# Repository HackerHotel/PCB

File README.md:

# PCB

This repository hosts the board files for the HackerHotel 2019 badge.

This is an EAGLE 8 (?) project. It should be possible to import it in
[KiCad](https://kicad-pcb.org)

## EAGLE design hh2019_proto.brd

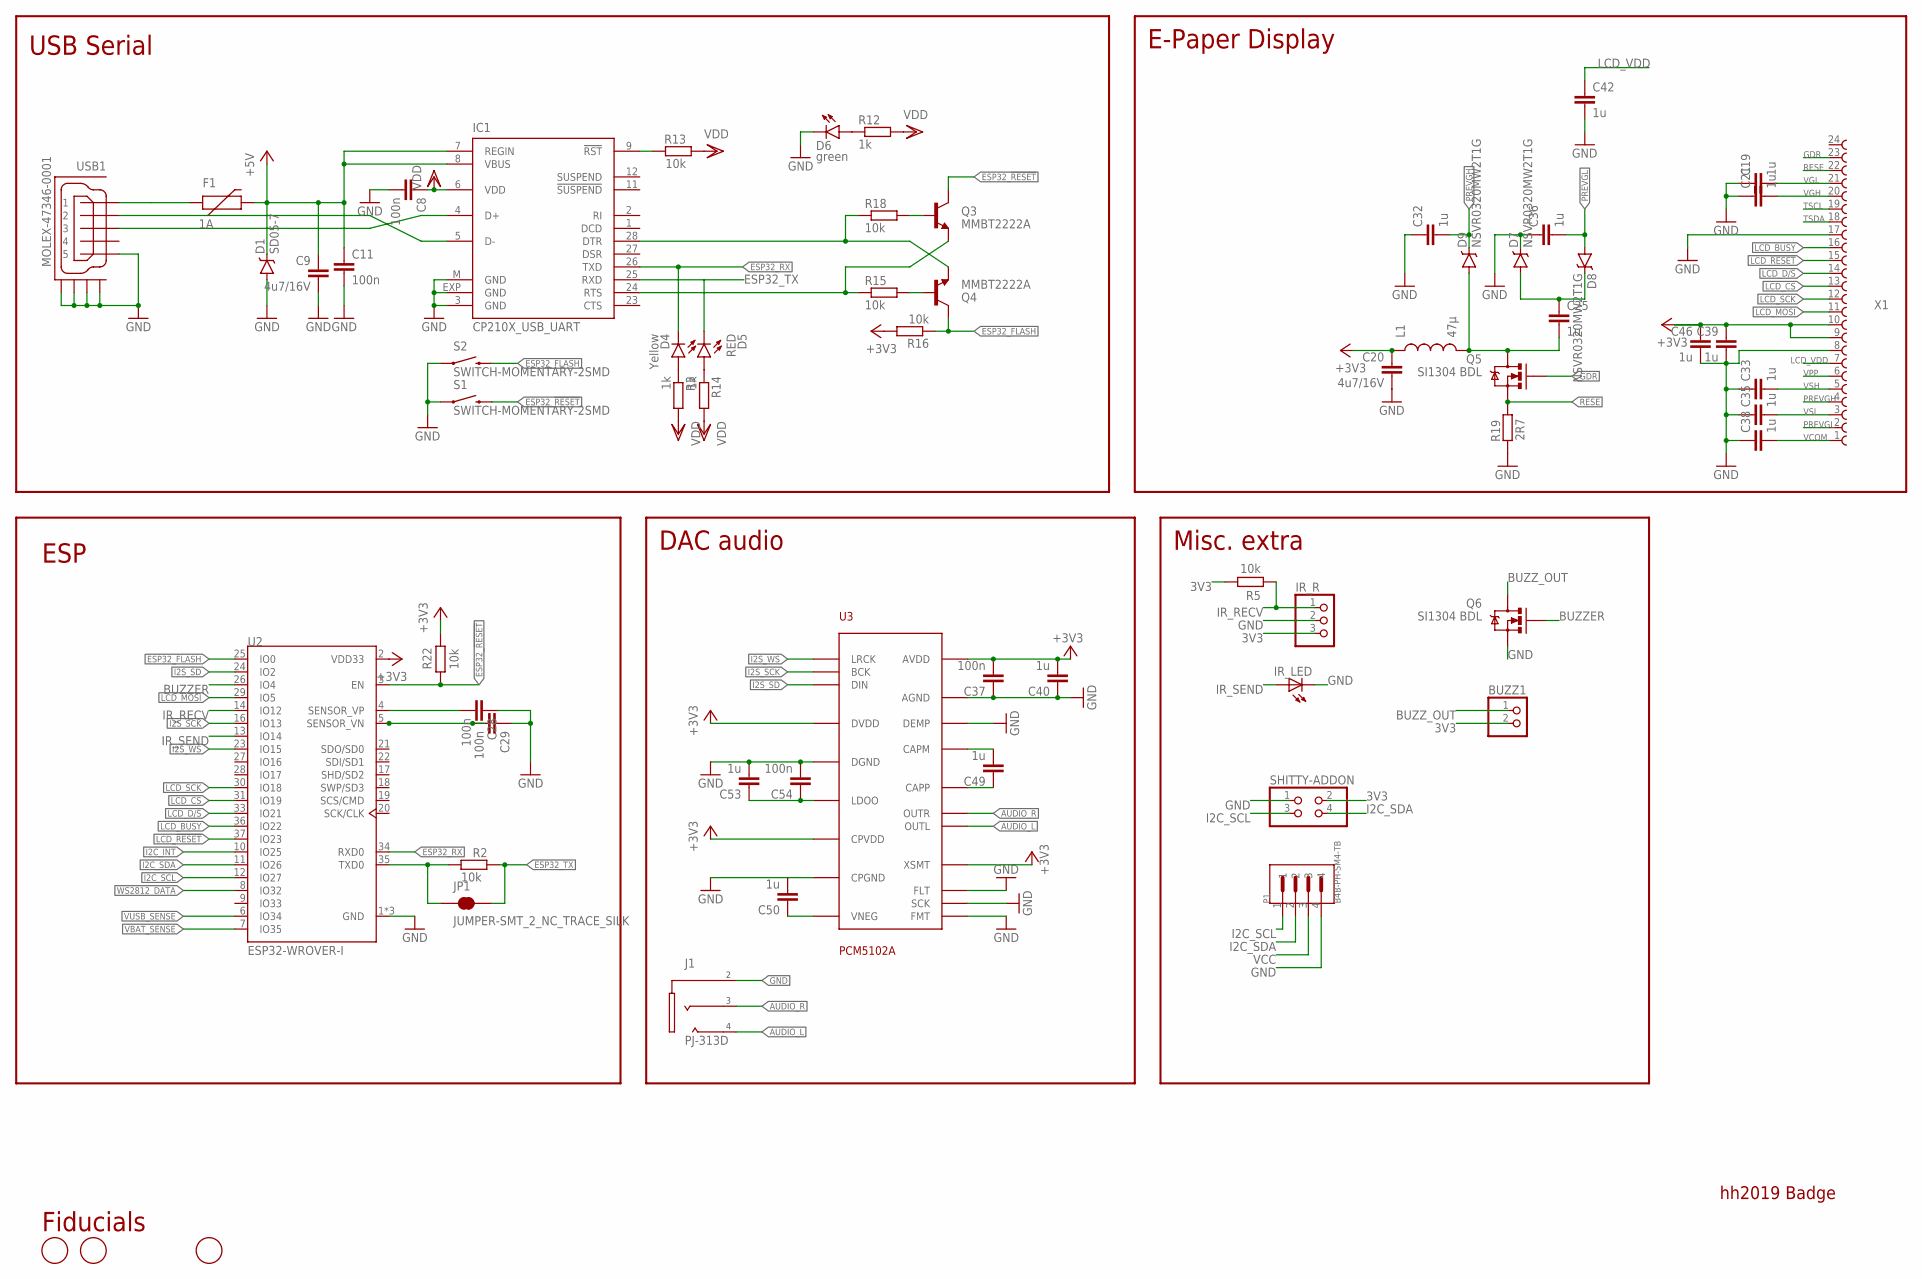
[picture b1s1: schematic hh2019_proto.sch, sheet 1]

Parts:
BUZZ1: PINHD-1X2; 1X02
C8, C11, C28, C29: 100n; C0603-DASHES; PARTNO GRM188R71H104KA93D
C9, C20: 4u7/16V; C0805; PARTNO GRM21BR61C475KA88K
C19, C21, C25, C32, C33, C35, C36, C38, C39, C42, C46: 1u; C0603-DASHES; PARTNO GRM188R61E105KA12D
C37, C54: 100n; C0603
C40, C49, C50, C53: 1u; C0603
D1: SD05-7; SOD-323; PARTNO SD05-7
D4: Yellow; LED-0603
D5: RED; LED-0603
D6: green; LED-0603
D7, D8, D9: NSVR0320MW2T1G; SOD-323; PARTNO BAT20JFILM
F1: 1A; PTC-1206
FD1, FD4, FD5: FIDUCIAL; FIDUCIAL_1MM; PARTNO NAP
IC1: CP210X_USB_UART; MLP28; PARTNO CP2102-GMR
IR_LED: LED5MM
IR_R: PINHD-1X3; 1X03
J1: PJ-313D
JP1: JUMPER-SMT_2_NC_TRACE_SILK; SMT-JUMPER_2_NC_TRACE_SILK
L1: 47µ; 1210; PARTNO NLCV32T-220K-EF
P1: B4B-PH-SM4-TB; JST_B4B-PH-SM4-TB
Q3, Q4: MMBT2222A; SOT23-3; PARTNO BC817-25,215
Q5, Q6: SI1304 BDL; SOT323; PARTNO SI1308EDL-T1-GE3
R2, R5, R13, R15, R16, R18, R22: 10k; R0603-DASHES; PARTNO ERJ-3GEYJ103V
R3, R12, R14: 1k; R0603-DASHES; PARTNO ERJ-3GEYJ102V
R19: 2R7; R0603-DASHES; PARTNO ERJ-3GEYJ5R1V
S1, S2: SWITCH-MOMENTARY-2SMD; TACTILE-SWITCH-SMD; PARTNO SKQGABE010
SHITTY-ADDON: PINHD-2X2; 2X02
U2: ESP32-WROVER-I; XCVR_ESP32-WROVER-I
U3: PCM5102A
USB1: MOLEX-47346-0001; MOLEX-47364-0001; PARTNO 10118192-0001LF
X1: 68712414022; PARTNO 68712414022

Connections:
3V3: BUZZ1.2, C20.1, C37.2, C39.1, C40.2, C46.1, IR_R.3, L1.1, R5.1, R16.2, R22.1, SHITTY-ADDON.2, U2.2 (VDD33), U3.P$1 (CPVDD), U3.P$8 (AVDD), U3.P$17 (XSMT), U3.P$20 (DVDD), X1.9, X1.10; also elsewhere on the board
+5V: C9.1, C11.1, D1.C, F1.2, IC1.7 (REGIN), IC1.8 (VBUS); also elsewhere on the board
AUDIO_L: J1.4_1 (4), J1.4_2 (4), U3.P$6 (OUTL)
AUDIO_R: J1.3_1 (3), J1.3_2 (3), U3.P$7 (OUTR)
BUZZER: Q6.1 (G), U2.26 (IO4)
BUZZ_OUT: BUZZ1.1, Q6.3 (D)
CAPM: C49.2, U3.P$4 (CAPM)
CAPP: C49.1, U3.P$2 (CAPP)
ESP32_!RESET: Q3.3 (C), R22.2, S1.3 (2), U2.3 (EN)
ESP32_FLASH: Q4.3 (C), R16.1, S2.3 (2), U2.25 (IO0)
ESP32_RX: D4.C, IC1.26 (TXD), U2.34 (RXD0)
ESP32_TX: D5.C, IC1.25 (RXD), JP1.2, R2.1
ESP32_TX_PRE: JP1.1, R2.2, U2.35 (TXD0)
GDR: Q5.1 (G), X1.23
GND: C8.2, C9.2, C11.2, C19.1, C20.2, C21.1, C28.1, C29.1, C32.1, C33.1, C35.1, C36.1, C37.1, C38.1, C39.2, C40.1, C42.2, C46.2, C50.2, C53.2, C54.2, D1.A, D6.C, D7.C, IC1.3 (GND), IC1.EXP (GND), IC1.M (GND), IR_LED.K (C), IR_R.2, J1.2_1 (2), J1.2_2 (2), P1.4, Q6.2 (S), R19.2, S1.1, S2.1, SHITTY-ADDON.1, U2.1 (GND), U2.15 (GND), U2.38 (GND), U3.P$3 (CPGND), U3.P$9 (AGND), U3.P$10 (DEMP), U3.P$11 (FLT), U3.P$12 (SCK), U3.P$16 (FMT), U3.P$19 (DGND), USB1.5, USB1.GND1, USB1.GND2, USB1.GND3, USB1.GND4, X1.8, X1.17; also elsewhere on the board
I2C_INT: U2.10 (IO25); also elsewhere on the board
I2C_SCL: P1.1, SHITTY-ADDON.3, U2.12 (IO27); also elsewhere on the board
I2C_SDA: P1.2, SHITTY-ADDON.4, U2.11 (IO26); also elsewhere on the board
I2S_SCK: U2.16 (IO13), U3.P$13 (BCK)
I2S_SD: U2.24 (IO2), U3.P$14 (DIN)
I2S_WS: U2.23 (IO15), U3.P$15 (LRCK)
IR_RECV: IR_R.1, R5.2, U2.14 (IO12)
IR_SEND: IR_LED.A, U2.13 (IO14)
LCD_!RESET: U2.37 (IO23), X1.15
LCD_BUSY: U2.36 (IO22), X1.16
LCD_CS: U2.31 (IO19), X1.13
LCD_D/!S: U2.33 (IO21), X1.14
LCD_MOSI: U2.29 (IO5), X1.11
LCD_SCK: U2.30 (IO18), X1.12
LCD_VDD: C42.1, X1.7
LDO0: C53.1, C54.1, U3.P$18 (LDOO)
unnamed: IC1.24 (RTS), Q3.2 (E), R15.1
unnamed: IC1.28 (DTR), Q4.2 (E), R18.1
unnamed: Q4.1 (B), R15.2
unnamed: Q3.1 (B), R18.2
unnamed: C25.1, D7.A, D8.C
unnamed: C25.2, D9.A, L1.2, Q5.3 (D)
unnamed: D6.A, R12.1
unnamed: D4.A, R3.1
unnamed: D5.A, R14.1
unnamed: F1.1, USB1.1
unnamed: C28.2, U2.4 (SENSOR_VP)
unnamed: C29.2, U2.5 (SENSOR_VN)
PREVGH: C32.2, D9.C, X1.4
PREVGL: C36.2, D8.A, X1.2
RESE: Q5.2 (S), R19.1, X1.22
RST: IC1.9 (!RST), R13.2
TSCL: X1.19
TSDA: X1.18
USB_DN_CON: IC1.5 (D-), USB1.2
USB_DP_CON: IC1.4 (D+), USB1.3
VBAT_SENSE: U2.7 (IO35); also elsewhere on the board
VCC: P1.3; also elsewhere on the board
VCOM: C38.2, X1.1
VDD: C8.1, IC1.6 (VDD), R3.2, R12.2, R13.1, R14.2
VGH: C21.2, X1.20
VGL: C19.2, X1.21
VNEG: C50.1, U3.P$5 (VNEG)
VPP: X1.6
VSH: C33.2, X1.5
VSL: C35.2, X1.3
VUSB_SENSE: U2.6 (IO34); also elsewhere on the board
WS2812_DATA: U2.8 (IO32); also elsewhere on the board

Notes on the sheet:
USB Serial
E-Paper Display
ESP
Fiducials
hh2019 Badge
DAC audio
Misc. extra

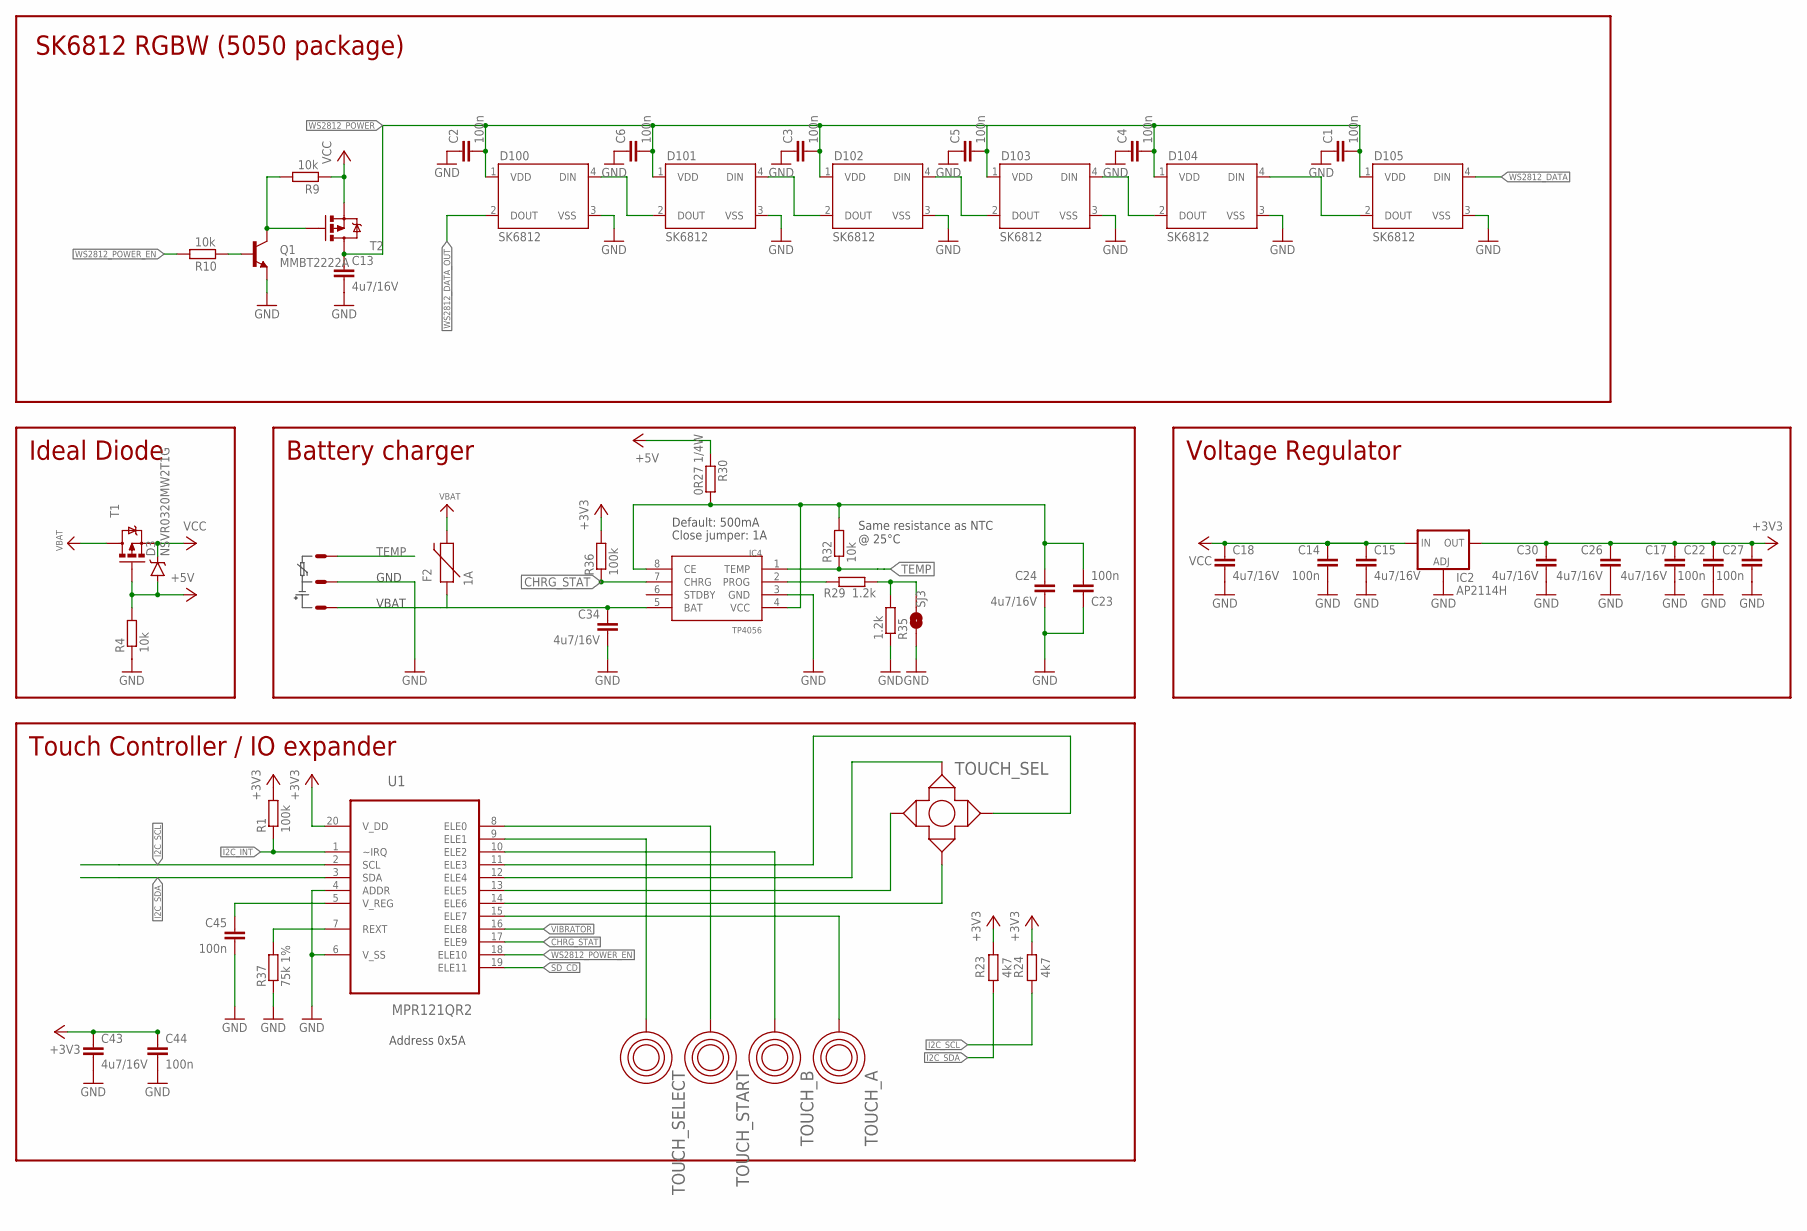
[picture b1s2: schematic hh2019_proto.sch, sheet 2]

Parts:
C1, C2, C3, C4, C5, C6, C14, C22, C23, C27, C44, C45: 100n; C0603-DASHES; PARTNO GRM188R71H104KA93D
C13, C15, C17, C18, C24, C26, C30, C34, C43: 4u7/16V; C0805; PARTNO GRM21BR61C475KA88K
D3: NSVR0320MW2T1G; SOD-323; PARTNO BAT20JFILM
D100, D101, D102, D103, D104, D105: SK6812; WS2812B; PARTNO SK6812
F2: 1A; PTC-1206
IC2: AP2114H; SOT223; PARTNO AP7215-33YG-13
IC4: TP4056; SOP-8
Q1: MMBT2222A; SOT23-3; PARTNO BC817-25,215
R1, R36: 100k; R0603-DASHES; PARTNO ERJ-3GEYJ104V
R4, R9, R10: 10k; R0603-DASHES; PARTNO ERJ-3GEYJ103V
R23, R24: 4k7; R0603-DASHES; PARTNO ERJ-3GEYJ103V
R29, R35: 1.2k; R0603-DASHES; PARTNO ERJ-3GEYJ222V
R30: 0R27 1/4W; R1206; PARTNO ERJ-3GEYJ154V
R32: 10k; R0603-DASHES; PARTNO ERJ-3GEYJ154V
R37: 75k 1%; R0603-DASHES; PARTNO ERJ-3GEYJ104V
SJ3: JUMPER-PAD-2-NOYES_SILK; PAD-JUMPER-2-NO_YES_SILK; PARTNO NAP
T1, T2: MOSFET-PCHANNEL; SOT23-3
TOUCH_A: TOUCHROUND; TOUCH_BUTTON; PARTNO NAP
TOUCH_B: TOUCHROUND; TOUCH_BUTTON; PARTNO NAP
TOUCH_SEL: TOUCH_CROSS; PARTNO NAP
TOUCH_SELECT: TOUCHSELECT; TOUCH_SELECT
TOUCH_START: TOUCHSELECT; TOUCH_SELECT
U1: MPR121QR2; QFN40P300X300X60-20N
X4: JST-PH3

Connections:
3V3: C17.1, C22.1, C26.1, C27.1, C30.1, C43.1, C44.1, IC2.4 (OUT), R1.2, R23.1, R24.1, R36.2, U1.20 (V_DD); also elsewhere on the board
+5V: D3.A, R4.2, R30.1, T1.1 (G); also elsewhere on the board
BAT: C34.1, F2.1, IC4.5 (BAT), X4.3
CE: C23.2, C24.1, IC4.4 (VCC), IC4.8 (CE), R30.2, R32.2
CHRG_STAT: IC4.7 (CHRG), R36.1, U1.17 (ELE9)
ELE0: TOUCH_START.P$1, U1.8 (ELE0)
ELE1: TOUCH_SELECT.P$1, U1.9 (ELE1)
ELE2: TOUCH_B.P$1, U1.10 (ELE2)
ELE3: TOUCH_SEL.R (RIGHT), U1.11 (ELE3)
ELE4: TOUCH_SEL.UP, U1.12 (ELE4)
ELE5: TOUCH_SEL.L (LEFT), U1.13 (ELE5)
ELE6: TOUCH_SEL.D (DOWN), U1.14 (ELE6)
ELE7: TOUCH_A.P$1, U1.15 (ELE7)
GND: C1.1, C2.1, C3.1, C4.1, C5.1, C6.1, C13.2, C14.2, C15.2, C17.2, C18.2, C22.2, C23.1, C24.2, C26.2, C27.2, C30.2, C34.2, C43.2, C44.2, C45.2, D100.3 (VSS), D101.3 (VSS), D102.3 (VSS), D103.3 (VSS), D104.3 (VSS), D105.3 (VSS), IC2.1 (ADJ), IC4.3 (GND), Q1.2 (E), R4.1, R35.2, R37.1, SJ3.1, U1.4 (ADDR), U1.6 (V_SS), X4.2; also elsewhere on the board
I2C_INT: R1.1, U1.1 (~IRQ); also elsewhere on the board
I2C_SCL: R24.2, U1.2 (SCL); also elsewhere on the board
I2C_SDA: R23.2, U1.3 (SDA); also elsewhere on the board
unnamed: D100.4 (DIN), D101.2 (DOUT)
unnamed: D103.4 (DIN), D104.2 (DOUT)
unnamed: D104.4 (DIN), D105.2 (DOUT)
unnamed: R29.2, R35.1, SJ3.2
unnamed: D101.4 (DIN), D102.2 (DOUT)
unnamed: C45.1, U1.5 (V_REG)
unnamed: R37.2, U1.7 (REXT)
unnamed: D102.4 (DIN), D103.2 (DOUT)
unnamed: Q1.1 (B), R10.2
unnamed: Q1.3 (C), R9.1, T2.1 (G)
PROG: IC4.2 (PROG), R29.1
SD_CD: U1.19 (ELE11)
TEMP: IC4.1 (TEMP), R32.1, X4.1
VBAT: F2.2, T1.3 (D); also elsewhere on the board
VCC: C14.1, C15.1, C18.1, D3.C, IC2.3 (IN), R9.2, T1.2 (S), T2.2 (S); also elsewhere on the board
VIBRATOR: U1.16 (ELE8)
WS2812_DATA: D105.4 (DIN); also elsewhere on the board
WS2812_DATA_OUT: D100.2 (DOUT)
WS2812_POWER: C1.2, C2.2, C3.2, C4.2, C5.2, C6.2, C13.1, D100.1 (VDD), D101.1 (VDD), D102.1 (VDD), D103.1 (VDD), D104.1 (VDD), D105.1 (VDD), T2.3 (D)
WS2812_POWER_EN: R10.1, U1.18 (ELE10)

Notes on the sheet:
Voltage Regulator
Battery charger
Ideal Diode
Default: 500mA
Close jumper: 1A
GND
VBAT
Same resistance as NTC @ 25°C
SK6812 RGBW (5050 package)
Touch Controller / IO expander
Address 0x5A

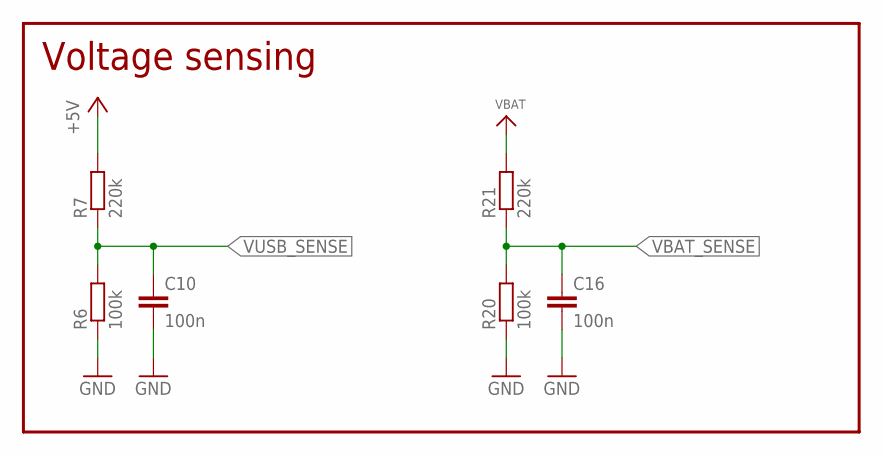
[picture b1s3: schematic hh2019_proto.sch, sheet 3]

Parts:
C10, C16: 100n; C0603-DASHES; PARTNO GRM188R71H104KA93D
R6, R20: 100k; R0603-DASHES; PARTNO ERJ-3GEYJ104V
R7, R21: 220k; R0603-DASHES; PARTNO ERJ-3GEYJ224V

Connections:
+5V: R7.2; also elsewhere on the board
GND: C10.2, C16.2, R6.1, R20.1; also elsewhere on the board
VBAT: R21.2; also elsewhere on the board
VBAT_SENSE: C16.1, R20.2, R21.1; also elsewhere on the board
VUSB_SENSE: C10.1, R6.2, R7.1; also elsewhere on the board

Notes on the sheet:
Voltage sensing

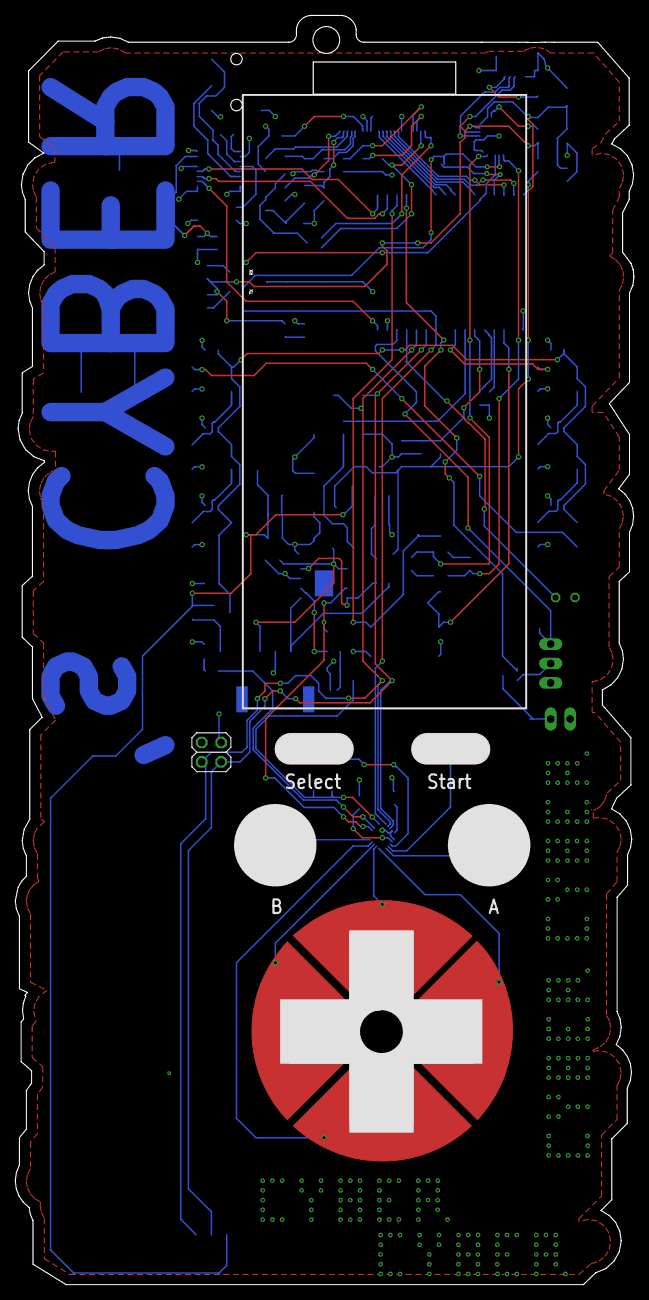
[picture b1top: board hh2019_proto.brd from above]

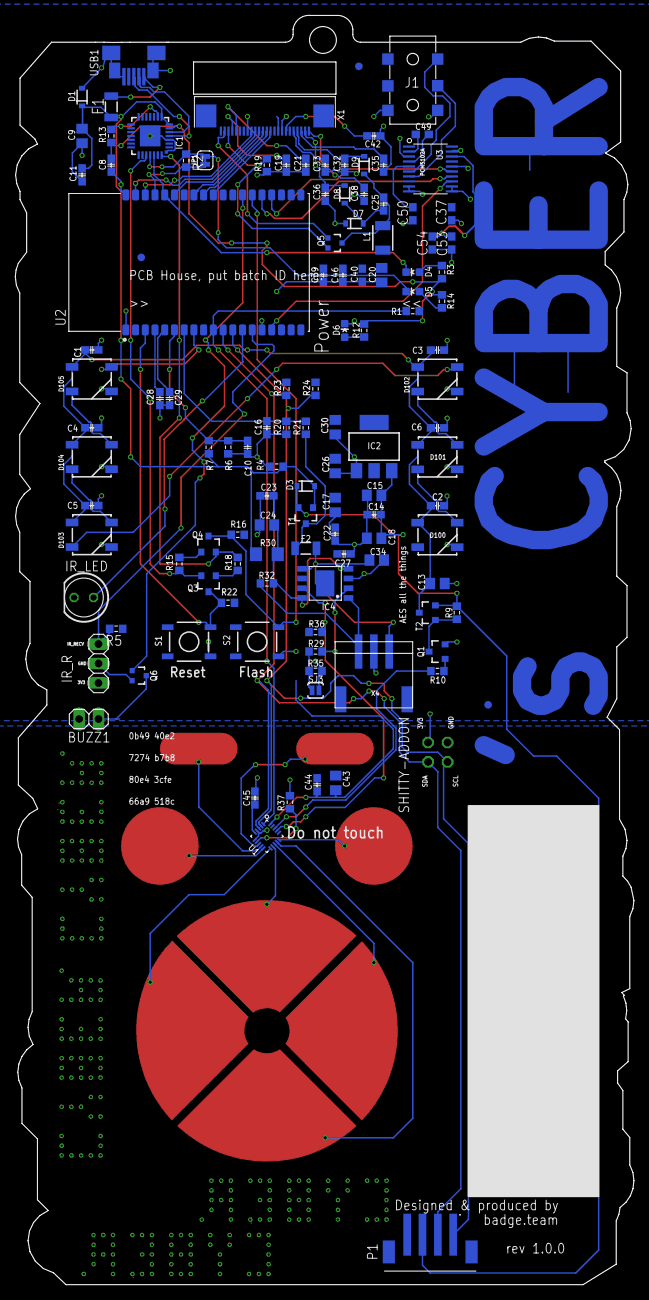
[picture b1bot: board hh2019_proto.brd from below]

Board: 2 copper layers, 80.8 x 165.7 mm, 124 parts (118 on the bottom side), 86 nets.

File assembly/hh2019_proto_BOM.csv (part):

"Part";"Value";"Device";"Package";"Description";"AVAILABILITY";"DESCRIPTION";"DIGI-KEY_PART_NUMBER";"DIGI-KEY_PURCHASE_URL";"MF";"MP";"MPN";"OC_FARNELL";"OC_NEWARK";"PACKAGE";"PARTNO";"PRICE";"PROD_ID";"SPICEPREFIX";"SUPPLIER";"VALUE";
"BUZZ1";"";"PINHD-1X2";"1X02";"PIN HEADER";"";"";"";"";"";"";"";"";"";"";"";"";"";"";"";"";
"C1";"100n";"C0603-DASHES";"C0603-DASHES";"";"";"";"";"";"";"";"";"";"";"";"GRM188R71H104KA93D";"";"";"";"";"";
"C2";"100n";"C0603-DASHES";"C0603-DASHES";"";"";"";"";"";"";"";"";"";"";"";"GRM188R71H104KA93D";"";"";"";"";"";
"C3";"100n";"C0603-DASHES";"C0603-DASHES";"";"";"";"";"";"";"";"";"";"";"";"GRM188R71H104KA93D";"";"";"";"";"";
"C4";"100n";"C0603-DASHES";"C0603-DASHES";"";"";"";"";"";"";"";"";"";"";"";"GRM188R71H104KA93D";"";"";"";"";"";
"C5";"100n";"C0603-DASHES";"C0603-DASHES";"";"";"";"";"";"";"";"";"";"";"";"GRM188R71H104KA93D";"";"";"";"";"";
"C6";"100n";"C0603-DASHES";"C0603-DASHES";"";"";"";"";"";"";"";"";"";"";"";"GRM188R71H104KA93D";"";"";"";"";"";
"C8";"100n";"C0603-DASHES";"C0603-DASHES";"";"";"";"";"";"";"";"";"";"";"";"GRM188R71H104KA93D";"";"";"";"";"";
"C9";"4u7/16V";"C-EUC0805";"C0805";"CAPACITOR, European symbol";"";"";"";"";"";"";"";"";"";"";"GRM21BR61C475KA88K";"";"";"";"";"";
"C10";"100n";"C0603-DASHES";"C0603-DASHES";"";"";"";"";"";"";"";"";"unknown";"";"";"GRM188R71H104KA93D";"";"";"";"";"";
"C11";"100n";"C0603-DASHES";"C0603-DASHES";"";"";"";"";"";"";"";"";"";"";"";"GRM188R71H104KA93D";"";"";"";"";"";
"C13";"4u7/16V";"C-EUC0805";"C0805";"CAPACITOR, European symbol";"";"";"";"";"";"";"";"";"";"";"GRM21BR61C475KA88K";"";"";"";"";"";
"C14";"100n";"C0603-DASHES";"C0603-DASHES";"";"";"";"";"";"";"";"";"";"";"";"GRM188R71H104KA93D";"";"";"";"";"";
"C15";"4u7/16V";"C-EUC0805";"C0805";"CAPACITOR, European symbol";"";"";"";"";"";"";"";"";"";"";"GRM21BR61C475KA88K";"";"";"";"";"";
"C16";"100n";"C0603-DASHES";"C0603-DASHES";"";"";"";"";"";"";"";"";"unknown";"";"";"GRM188R71H104KA93D";"";"";"";"";"";
"C17";"4u7/16V";"C-EUC0805";"C0805";"CAPACITOR, European symbol";"";"";"";"";"";"";"";"";"";"";"GRM21BR61C475KA88K";"";"";"";"";"";
"C18";"4u7/16V";"C-EUC0805";"C0805";"CAPACITOR, European symbol";"";"";"";"";"";"";"";"";"";"";"GRM21BR61C475KA88K";"";"";"";"";"";
"C19";"1u";"C0603-DASHES";"C0603-DASHES";"";"";"";"";"";"";"";"";"";"";"";"GRM188R61E105KA12D";"";"";"";"";"";
"C20";"4u7/16V";"C-EUC0805";"C0805";"CAPACITOR, European symbol";"";"";"";"";"";"";"";"";"";"";"GRM21BR61C475KA88K";"";"";"";"";"";
"C21";"1u";"C0603-DASHES";"C0603-DASHES";"";"";"";"";"";"";"";"";"";"";"";"GRM188R61E105KA12D";"";"";"";"";"";
"C22";"100n";"C0603-DASHES";"C0603-DASHES";"";"";"";"";"";"";"";"";"";"";"";"GRM188R71H104KA93D";"";"";"";"";"";
"C23";"100n";"C0603-DASHES";"C0603-DASHES";"";"";"";"";"";"";"";"";"";"";"";"GRM188R71H104KA93D";"";"";"";"";"";
"C24";"4u7/16V";"C-EUC0805";"C0805";"CAPACITOR, European symbol";"";"";"";"";"";"";"";"";"";"";"GRM21BR61C475KA88K";"";"";"";"";"";
"C25";"1u";"C0603-DASHES";"C0603-DASHES";"";"";"";"";"";"";"";"";"";"";"";"GRM188R61E105KA12D";"";"";"";"";"";
"C26";"4u7/16V";"C-EUC0805";"C0805";"CAPACITOR, European symbol";"";"";"";"";"";"";"";"";"";"";"GRM21BR61C475KA88K";"";"";"";"";"";
"C27";"100n";"C0603-DASHES";"C0603-DASHES";"";"";"";"";"";"";"";"";"";"";"";"GRM188R71H104KA93D";"";"";"";"";"";
"C28";"100n";"C0603-DASHES";"C0603-DASHES";"";"";"";"";"";"";"";"";"unknown";"";"";"GRM188R71H104KA93D";"";"";"";"";"";
"C29";"100n";"C0603-DASHES";"C0603-DASHES";"";"";"";"";"";"";"";"";"unknown";"";"";"GRM188R71H104KA93D";"";"";"";"";"";
"C30";"4u7/16V";"C-EUC0805";"C0805";"CAPACITOR, European symbol";"";"";"";"";"";"";"";"";"";"";"GRM21BR61C475KA88K";"";"";"";"";"";
"C32";"1u";"C0603-DASHES";"C0603-DASHES";"";"";"";"";"";"";"";"";"";"";"";"GRM188R61E105KA12D";"";"";"";"";"";
"C33";"1u";"C0603-DASHES";"C0603-DASHES";"";"";"";"";"";"";"";"";"";"";"";"GRM188R61E105KA12D";"";"";"";"";"";
"C34";"4u7/16V";"C-EUC0805";"C0805";"CAPACITOR, European symbol";"";"";"";"";"";"";"";"";"";"";"GRM21BR61C475KA88K";"";"";"";"";"";
"C35";"1u";"C0603-DASHES";"C0603-DASHES";"";"";"";"";"";"";"";"";"";"";"";"GRM188R61E105KA12D";"";"";"";"";"";
"C36";"1u";"C0603-DASHES";"C0603-DASHES";"";"";"";"";"";"";"";"";"";"";"";"GRM188R61E105KA12D";"";"";"";"";"";
"C37";"100n";"C-EUC0603";"C0603";"CAPACITOR, European symbol";"";"";"";"";"";"";"";"";"";"";"";"";"";"C";"";"";
"C38";"1u";"C0603-DASHES";"C0603-DASHES";"";"";"";"";"";"";"";"";"";"";"";"GRM188R61E105KA12D";"";"";"";"";"";
"C39";"1u";"C0603-DASHES";"C0603-DASHES";"";"";"";"";"";"";"";"";"";"";"";"GRM188R61E105KA12D";"";"";"";"";"";
"C40";"1u";"C-EUC0603";"C0603";"CAPACITOR, European symbol";"";"";"";"";"";"";"";"";"";"";"";"";"";"C";"";"";
"C42";"1u";"C0603-DASHES";"C0603-DASHES";"";"";"";"";"";"";"";"";"";"";"";"GRM188R61E105KA12D";"";"";"";"";"";
"C43";"4u7/16V";"C-EUC0805";"C0805";"CAPACITOR, European symbol";"";"";"";"";"";"";"";"";"";"";"GRM21BR61C475KA88K";"";"";"";"";"";
"C44";"100n";"C0603-DASHES";"C0603-DASHES";"";"";"";"";"";"";"";"";"";"";"";"GRM188R71H104KA93D";"";"";"";"";"";
"C45";"100n";"C0603-DASHES";"C0603-DASHES";"";"";"";"";"";"";"";"";"";"";"";"GRM188R71H104KA93D";"";"";"";"";"";
"C46";"1u";"C0603-DASHES";"C0603-DASHES";"";"";"";"";"";"";"";"";"";"";"";"GRM188R61E105KA12D";"";"";"";"";"";
"C49";"1u";"C-EUC0603";"C0603";"CAPACITOR, European symbol";"";"";"";"";"";"";"";"";"";"";"";"";"";"C";"";"";
"C50";"1u";"C-EUC0603";"C0603";"CAPACITOR, European symbol";"";"";"";"";"";"";"";"";"";"";"";"";"";"C";"";"";
"C53";"1u";"C-EUC0603";"C0603";"CAPACITOR, European symbol";"";"";"";"";"";"";"";"";"";"";"";"";"";"C";"";"";
"C54";"100n";"C-EUC0603";"C0603";"CAPACITOR, European symbol";"";"";"";"";"";"";"";"";"";"";"";"";"";"C";"";"";
"D1";"SD05-7";"DIODE-SCHOTTKY-PMEG4005EJ";"SOD-323";"Schottky diodes in SFE's production catalog";"";"";"";"";"";"";"";"";"";"";"SD05-7";"";"DIO-10955";"";"";"PMEG4005EJ";
"D3";"NSVR0320MW2T1G";"BAT20JFILM";"SOD-323";"23V, 1A Schottky diode, SOD-323 package";"";"";"";"";"";"";"";"";"";"";"BAT20JFILM";"";"DIO-11623";"";"";"BAT20JFILM";
"D4";"Yellow";"LED0603";"LED-0603";"LEDs";"";"";"";"";"";"";"";"";"";"";"";"";"";"";"";"";
"D5";"RED";"LED0603";"LED-0603";"LEDs";"";"";"";"";"";"";"";"";"";"";"";"";"";"";"";"";
"D6";"green";"LED0603";"LED-0603";"LEDs";"";"";"";"";"";"";"";"";"";"";"";"";"";"";"";"";
"D7";"NSVR0320MW2T1G";"BAT20JFILM";"SOD-323";"23V, 1A Schottky diode, SOD-323 package";"";"";"";"";"";"";"";"";"";"";"BAT20JFILM";"";"DIO-11623";"";"";"BAT20JFILM";
"D8";"NSVR0320MW2T1G";"BAT20JFILM";"SOD-323";"23V, 1A Schottky diode, SOD-323 package";"";"";"";"";"";"";"";"";"";"";"BAT20JFILM";"";"DIO-11623";"";"";"BAT20JFILM";
"D9";"NSVR0320MW2T1G";"BAT20JFILM";"SOD-323";"23V, 1A Schottky diode, SOD-323 package";"";"";"";"";"";"";"";"";"";"";"BAT20JFILM";"";"DIO-11623";"";"";"BAT20JFILM";
"D100";"SK6812";"WS2812B";"WS2812B";"WS2812B - Intelligent control LED integrated light source";"";"";"";"";"";"";"";"";"";"";"SK6812";"";"";"";"";"";
"D101";"SK6812";"WS2812B";"WS2812B";"WS2812B - Intelligent control LED integrated light source";"";"";"";"";"";"";"";"";"";"";"SK6812";"";"";"";"";"";
"D102";"SK6812";"WS2812B";"WS2812B";"WS2812B - Intelligent control LED integrated light source";"";"";"";"";"";"";"";"";"";"";"SK6812";"";"";"";"";"";
"D103";"SK6812";"WS2812B";"WS2812B";"WS2812B - Intelligent control LED integrated light source";"";"";"";"";"";"";"";"";"";"";"SK6812";"";"";"";"";"";
"D104";"SK6812";"WS2812B";"WS2812B";"WS2812B - Intelligent control LED integrated light source";"";"";"";"";"";"";"";"";"";"";"SK6812";"";"";"";"";"";
"D105";"SK6812";"WS2812B";"WS2812B";"WS2812B - Intelligent control LED integrated light source";"";"";"";"";"";"";"";"";"";"";"SK6812";"";"";"";"";"";
"F1";"1A";"PTCSMD";"PTC-1206";"Resettable Fuse PTC";"";"";"";"";"";"";"";"";"";"";"";"";"RES-11150";"";"";"";
"F2";"1A";"PTCSMD";"PTC-1206";"Resettable Fuse PTC";"";"";"";"";"";"";"";"";"";"";"";"";"RES-11150";"";"";"";
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
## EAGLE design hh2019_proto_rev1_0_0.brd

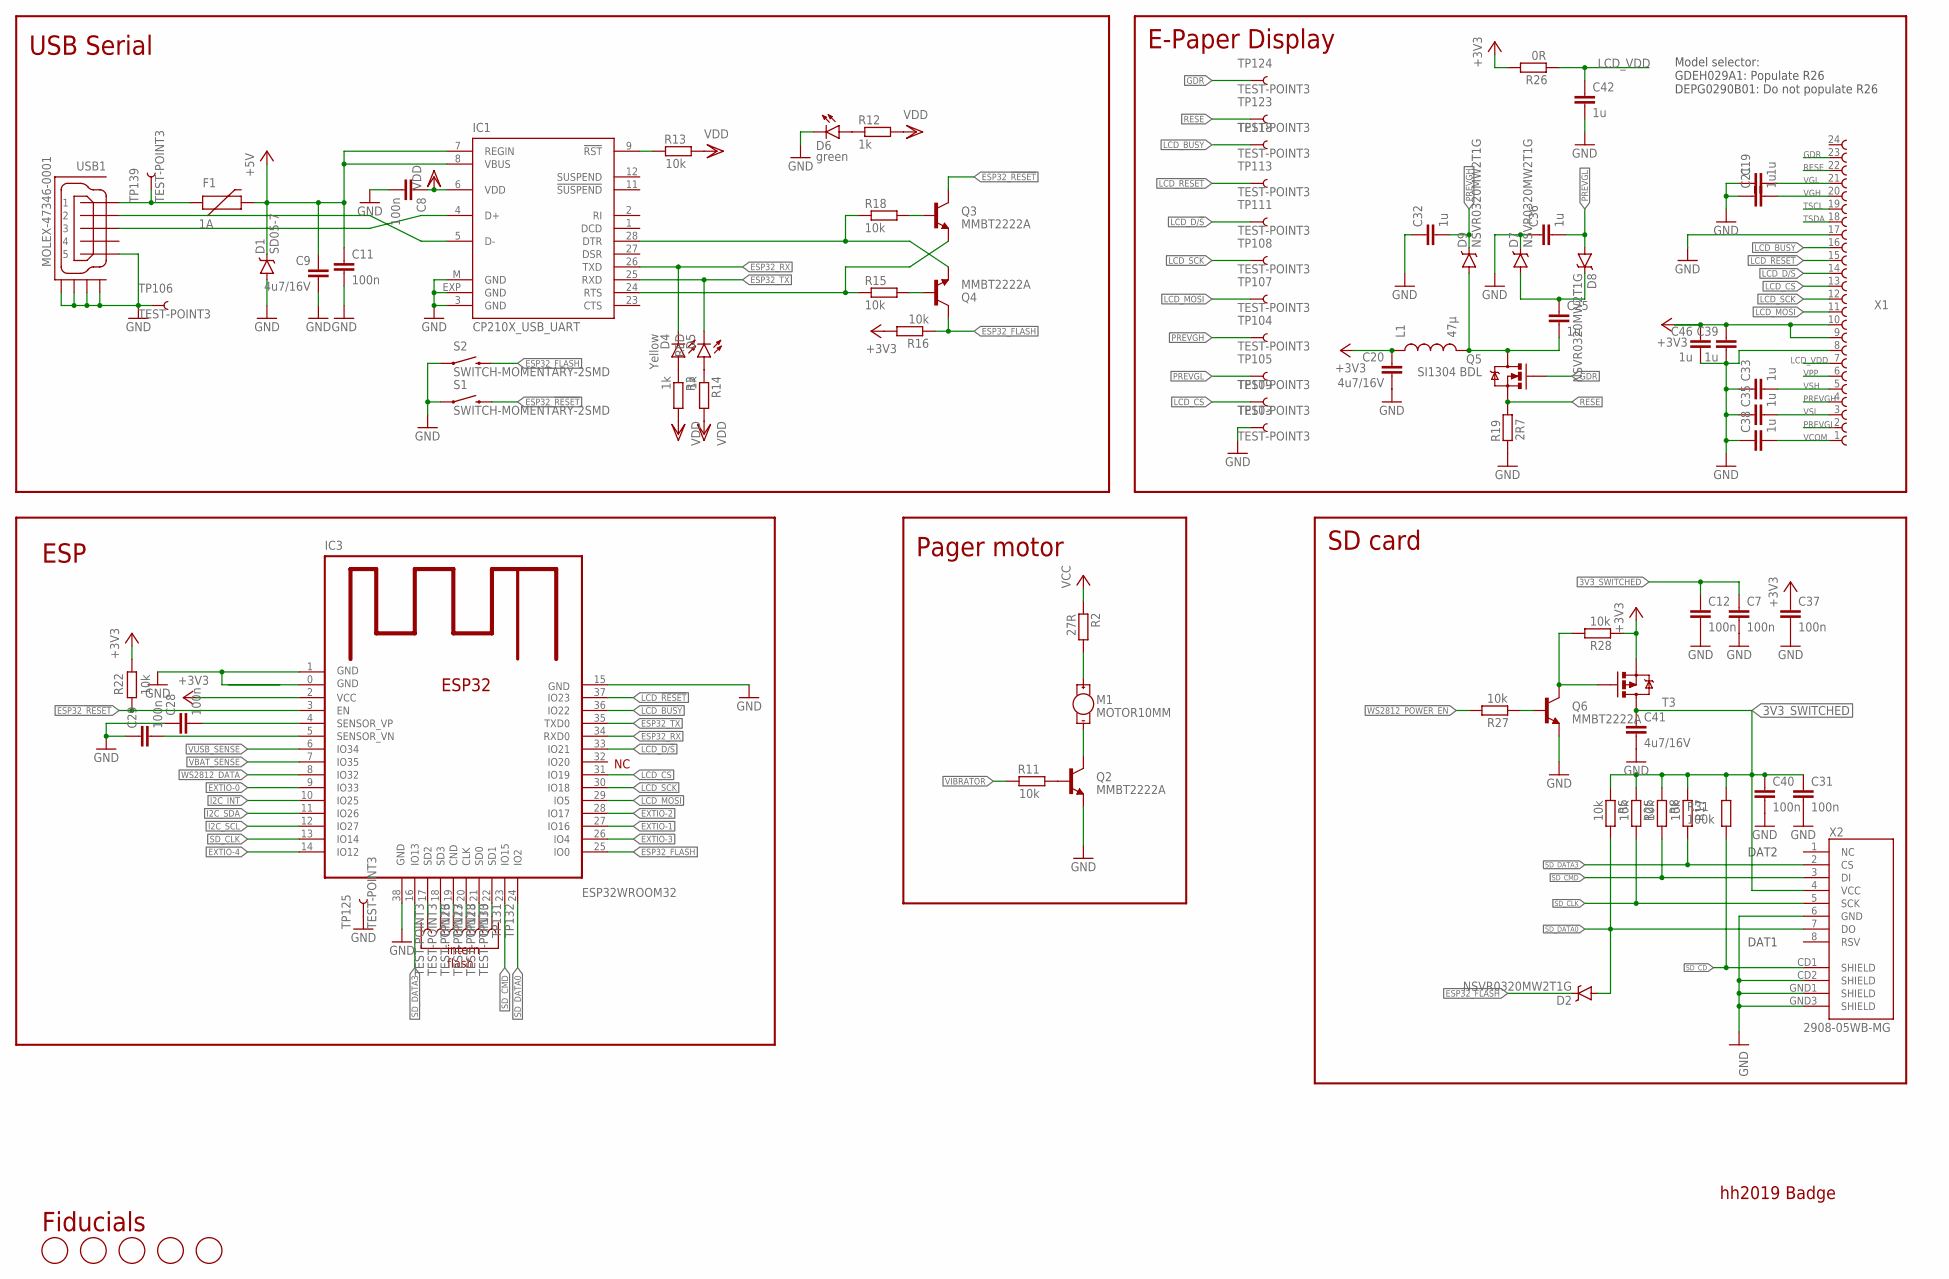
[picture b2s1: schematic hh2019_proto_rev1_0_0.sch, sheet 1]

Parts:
C7, C8, C11, C12, C28, C29, C31, C37, C40: 100n; C0603-DASHES; PARTNO GRM188R71H104KA93D
C9, C20, C41: 4u7/16V; C0805; PARTNO GRM21BR61C475KA88K
C19, C21, C25, C32, C33, C35, C36, C38, C39, C42, C46: 1u; C0603-DASHES; PARTNO GRM188R61E105KA12D
D1: SD05-7; SOD-323; PARTNO SD05-7
D2, D7, D8, D9: NSVR0320MW2T1G; SOD-323; PARTNO BAT20JFILM
D4: Yellow; LED-0603
D5: RED; LED-0603
D6: green; LED-0603
F1: 1A; PTC-1206
FD1, FD2, FD3, FD4, FD5: FIDUCIAL; FIDUCIAL_1MM; PARTNO NAP
IC1: CP210X_USB_UART; MLP28; PARTNO CP2102-GMR
IC3: ESP32WROOM32; ESP32MOD
L1: 47µ; 1210; PARTNO NLCV32T-220K-EF
M1: MOTOR10MM; VIBE-MOTOR-10MM
Q2, Q3, Q4, Q6: MMBT2222A; SOT23-3; PARTNO BC817-25,215
Q5: SI1304 BDL; SOT323; PARTNO SI1308EDL-T1-GE3
R2: 27R; R1206; PARTNO ERJ-3GEYJ220V
R3, R12, R14: 1k; R0603-DASHES; PARTNO ERJ-3GEYJ102V
R5, R8, R11, R13, R15, R16, R17, R18, R22, R25, R27, R28: 10k; R0603-DASHES; PARTNO ERJ-3GEYJ103V
R19: 2R7; R0603-DASHES; PARTNO ERJ-3GEYJ5R1V
R26: 0R; R0603-DASHES; PARTNO ERJ-3GEYJ5R1V
R31: 100k; R0603-DASHES; PARTNO ERJ-3GEYJ104V
S1, S2: SWITCH-MOMENTARY-2SMD; TACTILE-SWITCH-SMD; PARTNO SKQGABE010
T3: MOSFET-PCHANNEL; SOT23-3
TP103, TP104, TP105, TP106, TP107, TP108, TP109, TP111, TP113, TP118, TP123, TP124, TP125, TP126, TP127, TP128, TP130, TP131, TP132, TP139: TEST-POINT3; PAD.03X.03; PARTNO NAP
USB1: MOLEX-47346-0001; MOLEX-47364-0001; PARTNO 10118192-0001LF
X1: 68712414022; PARTNO 68712414022
X2: 2908-05WB-MG; MICRO-SD-SOCKET-PP; PARTNO 2908-05WB-MG

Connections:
3V3_SWITCHED: C7.1, C12.1, C31.1, C40.1, C41.1, R5.2, R8.2, R17.2, R25.2, R31.1, T3.3 (D), X2.4 (VCC); also elsewhere on the board
+3V3: C20.1, C37.1, C39.1, C46.1, IC3.2 (VCC), L1.1, R16.2, R22.1, R26.1, R28.2, T3.2 (S), X1.9, X1.10; also elsewhere on the board
+5V: C9.1, C11.1, D1.C, F1.2, IC1.7 (REGIN), IC1.8 (VBUS); also elsewhere on the board
CD0: IC3.21 (SD0), TP131.P$1
CLK: IC3.20 (CLK), TP130.P$1
CND: IC3.19 (CND), TP128.P$1
ESP32_!RESET: IC3.3 (EN), Q3.3 (C), R22.2, S1.3 (2); also elsewhere on the board
ESP32_FLASH: D2.C, IC3.25 (IO0), Q4.3 (C), R16.1, S2.3 (2); also elsewhere on the board
ESP32_RX: D4.C, IC1.26 (TXD), IC3.34 (RXD0); also elsewhere on the board
ESP32_TX: D5.C, IC1.25 (RXD), IC3.35 (TXD0); also elsewhere on the board
EXTIO-0: IC3.9 (IO33); also elsewhere on the board
EXTIO-1: IC3.27 (IO16); also elsewhere on the board
EXTIO-2: IC3.28 (IO17); also elsewhere on the board
EXTIO-3: IC3.26 (IO4); also elsewhere on the board
EXTIO-4: IC3.14 (IO12); also elsewhere on the board
GDR: Q5.1 (G), TP124.P$1, X1.23
GND: C7.2, C8.2, C9.2, C11.2, C12.2, C19.1, C20.2, C21.1, C28.1, C29.1, C31.2, C32.1, C33.1, C35.1, C36.1, C37.2, C38.1, C39.2, C40.2, C41.2, C42.2, C46.2, D1.A, D6.C, D7.C, IC1.3 (GND), IC1.EXP (GND), IC1.M (GND), IC3.0 (GND), IC3.1 (GND), IC3.15 (GND), IC3.38 (GND), Q2.2 (E), Q6.2 (E), R19.2, S1.1, S2.1, TP103.P$1, TP106.P$1, TP125.P$1, USB1.5, USB1.GND1, USB1.GND2, USB1.GND3, USB1.GND4, X1.8, X1.17, X2.6 (GND), X2.CD2 (SHIELD), X2.GND1 (SHIELD), X2.GND3 (SHIELD); also elsewhere on the board
I2C_INT: IC3.10 (IO25); also elsewhere on the board
I2C_SCL: IC3.12 (IO27); also elsewhere on the board
I2C_SDA: IC3.11 (IO26); also elsewhere on the board
LCD_!RESET: IC3.37 (IO23), TP113.P$1, X1.15
LCD_BUSY: IC3.36 (IO22), TP118.P$1, X1.16
LCD_CS: IC3.31 (IO19), TP109.P$1, X1.13
LCD_D/!S: IC3.33 (IO21), TP111.P$1, X1.14
LCD_MOSI: IC3.29 (IO5), TP107.P$1, X1.11
LCD_SCK: IC3.30 (IO18), TP108.P$1, X1.12
LCD_VDD: C42.1, R26.2, X1.7
unnamed: IC1.9 (!RST), R13.2
unnamed: IC1.24 (RTS), Q3.2 (E), R15.1
unnamed: IC1.28 (DTR), Q4.2 (E), R18.1
unnamed: Q4.1 (B), R15.2
unnamed: Q3.1 (B), R18.2
unnamed: Q6.1 (B), R27.2
unnamed: M1.-, Q2.3 (C)
unnamed: Q6.3 (C), R28.1, T3.1 (G)
unnamed: M1.+, R2.1
unnamed: C25.1, D7.A, D8.C
unnamed: C25.2, D9.A, L1.2, Q5.3 (D)
unnamed: D6.A, R12.1
unnamed: D4.A, R3.1
unnamed: D5.A, R14.1
unnamed: F1.1, TP139.P$1, USB1.1
unnamed: C28.2, IC3.4 (SENSOR_VP)
unnamed: C29.2, IC3.5 (SENSOR_VN)
unnamed: Q2.1 (B), R11.1
PREVGH: C32.2, D9.C, TP104.P$1, X1.4
PREVGL: C36.2, D8.A, TP105.P$1, X1.2
RESE: Q5.2 (S), R19.1, TP123.P$1, X1.22
SD1: IC3.22 (SD1), TP132.P$1
SD2: IC3.17 (SD2), TP126.P$1
SD3: IC3.18 (SD3), TP127.P$1
SD_CD: R31.2, X2.CD1 (SHIELD); also elsewhere on the board
SD_CLK: IC3.13 (IO14), R25.1, X2.5 (SCK)
SD_CMD: IC3.23 (IO15), R8.1, X2.3 (DI)
SD_DATA0: D2.A, IC3.24 (IO2), R5.1, X2.7 (DO)
SD_DATA3: IC3.16 (IO13), R17.1, X2.2 (CS)
TSCL: X1.19
TSDA: X1.18
USB_DN_CON: IC1.5 (D-), USB1.2; also elsewhere on the board
USB_DP_CON: IC1.4 (D+), USB1.3; also elsewhere on the board
VBAT_SENSE: IC3.7 (IO35); also elsewhere on the board
VCC: R2.2; also elsewhere on the board
VCOM: C38.2, X1.1
VDD: C8.1, IC1.6 (VDD), R3.2, R12.2, R13.1, R14.2
VGH: C21.2, X1.20
VGL: C19.2, X1.21
VIBRATOR: R11.2; also elsewhere on the board
VPP: X1.6
VSH: C33.2, X1.5
VSL: C35.2, X1.3
VUSB_SENSE: IC3.6 (IO34); also elsewhere on the board
WS2812_DATA: IC3.8 (IO32); also elsewhere on the board
WS2812_POWER_EN: R27.1; also elsewhere on the board

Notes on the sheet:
USB Serial
E-Paper Display
SD card
intern flash
ESP
Fiducials
Pager motor
DAT1
DAT2
Model selector: GDEH029A1: Populate R26 DEPG0290B01: Do not populate R26
hh2019 Badge

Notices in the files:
parts and their libraries:
SparkFun-DigitalIC: Licensing: Creative Commons ShareAlike 4.0 International - https://creativecommons.org/licenses/by-sa/4.0
EAGLE-FPC_CONNECTOR_AND_FFC_CAB-rev1: Copyright: Würth Elektronik
